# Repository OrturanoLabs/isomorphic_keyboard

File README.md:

# Isomorphic keyboard

An open-source, **modular isomorphic keyboard**. The instrument is built from identical
12-key tiles arranged in supported column-based grids. A pico-ice (Lattice iCE40UP5K)
rediscovers the arrangement on every scan and plays it over **MIDI**. Tiles can be added,
removed and moved while playing.

## Status

- **rev A** (tag `rev-a-prototype`): working prototype. Double-stack tiles (key board over
  logic board), hot-plug, automatic above/below/beside detection, MIDI DIN output.
- **Current development:** a single-PCB tile with Cherry-MX-style SMD hot-swap
  sockets, a practical equilateral lattice and chassis-supported drop-in contacts.
  The **tiny FPGA is the lead implementation**, with discrete logic retained as
  the no-programmer reference and alternative. Target: 20 MHz shift clock,
  up to 16 tiles; no tile-side MCU, LEDs or Hall sensing.
- **rev B** (reference commit `d358953`): termination, decoupling and assembly
  studies for the earlier double-board design; not hardware-tested.

The project is consolidated into this one directory. Start with the
[current status](docs/architecture/current-development.md) and
[ordered FPGA plan](docs/FPGA_PLAN.md); migration details are in the
[consolidation record](docs/CONSOLIDATION.md). The FPGA/controller tests have
advanced, but the new tile is not yet a routed, hardware-validated release.

## Repository layout

| Path | Content |
|---|---|
| `docs/` | documentation: [index](docs/index.md), [engineering ledger](docs/LEDGER.md) |
| `hardware/experiments/simple-tile/fpga/` | active FPGA RTL, chain tests and board prototype |
| `hardware/experiments/simple-tile/discrete-spld/` | discrete baseline; SPLD comparison retained as reference |
| `hardware/experiments/simple-tile/connector-next/` | current chassis-contact and tiling study |
| `hardware/kicad/tile/` | reference KiCad key board + logic board |
| `hardware/simulation/` | behavioural VHDL model of a tile and grid testbenches |
| `hardware/fabrication/rev-a/` | gerbers and BOM of the manufactured rev-A boards |
| `firmware/ice40/` | controller firmware (VHDL) for the pico-ice |
| `firmware/ice40/scan20/` | isolated 20 MHz / 16-tile scan-engine test fixture |
| `firmware/experiments/` | earlier bring-up designs, kept for reference |
| `tools/` | rootless container recipes, `kicad-cli` / OSS CAD Suite wrappers, check scripts |
| `LICENSES/` | full license texts |

## Quick start

Current development checks, from the repository root:

```sh
bash hardware/experiments/simple-tile/fpga/sim/run_sims.sh
bash firmware/ice40/scan20/sim/run_sims.sh
```

The following commands build/open the earlier reference implementation:

```sh
# firmware (rootless podman)
podman build -t localhost/oss-cad-suite:2026-09-26 tools/containers/oss-cad-suite
cd firmware/ice40 && ../../tools/oss.sh make && make upload-flash

# hardware
flatpak install --user flathub org.kicad.KiCad
flatpak run org.kicad.KiCad hardware/kicad/tile/isomorphic_tile.kicad_pro
```

See [docs/build/firmware.md](docs/build/firmware.md) and
[docs/build/hardware.md](docs/build/hardware.md).

## Licenses

| Part | License |
|---|---|
| Hardware (`hardware/`) | CERN-OHL-S v2 |
| Firmware and tools (`firmware/`, `tools/`) | GPL-3.0 |
| Documentation (`docs/`) | CC BY 4.0 |
| Vendored Open Logic subset (`firmware/ice40/src/open-logic/`) | PSI HDL Library License 1.0 |

Full texts are in `LICENSES/`. Each top-level folder has its own `LICENSE.md`.

© Orturano Labs

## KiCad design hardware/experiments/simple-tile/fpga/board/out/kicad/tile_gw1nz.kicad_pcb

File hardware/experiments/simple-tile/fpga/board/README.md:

# fpga/board -- single-PCB FPGA tile: placement + circuit prototype

Owner: fpga-board worker. Package/board facts come from vendor documents
(sha256-stamped in `data/*.json`) and machine checks in `tools/`; nothing
here is inferred from synthesis tool behavior.

## Layout

- `data/pins_gw1nz_qn48.json`, `data/pins_ice40up_sg48.json` -- per-pin
  provenance DBs (role, rail, vendor doc + section + sha256) for the two
  candidates. Pin 9 (GW1NZ) is excluded: automotive UG846 disagrees with
  commercial UG842 on it (VCC vs IOR2A) -- order-code hazard.
- `constraints/tile_gw1nz_board.cst`, `tile_up5k_board.pcf` -- PRODUCTION
  pin maps (26 tile IOs verified against the vendor tables; JTAG/config/
  strap pads reserved). These supersede `fpga/synth/*` (empirical chipdb
  probe proposals). Do not edit `fpga/**` from here.
- `kicad/board_gen.py` -- deterministic board builder (corrected revc
  TileTiling outline, 12 Kailh sockets, 19 connector-next chassis pads,
  passives, TPs), self-check gates GK1..GK7.
- `kicad/gen_footprints.py` -- the two custom QFN48 footprints.
- `kicad/lib/fpga_board.pretty/` -- generated custom footprints.
- `tools/pincon_check.py` -- constraint-vs-vendor-table checker (B1..B6,
  H1, S1; both variants PASS).
- `tools/footprint_verify.py` -- footprint land pattern vs vendor package
  dims, incl. negative control (both PASS; UP5K land = LAND-TBD).
- `tools/board_net_check.py` -- netlist/power-pin binding checker on the
  emitted .kicad_pcb, incl. negative controls (both PASS).
- `tools/run_board_pnr.sh` -- real yosys/nextpnr PnR of the fpga
  workstream's RTL (read-only) against the production maps (PASS;
  `RUN_VARIANTS="gw1nz"` narrows a re-run when only one cst changed).
- `kicad/sch_gen.py` -- authoritative schematic generator (gw1nz):
  emits `out/kicad/tile_gw1nz.kicad_sch` + local symbol lib. TRUE KiCad
  ERC at severity-all = **0 violations, no exclusions**
  (`out/kicad/tile_gw1nz.erc.json`).
- `tools/schematic_check.py` -- schematic<->board<->cst reconciliation
  S1..S7 + 3 negative controls (fresh ERC rerun, 45-net census,
  pad parity 144==144, cst port<->net<->pin mapping, strap + series
  node-set checks) -- PASS.
- `tools/drive_attr_ab.sh` -- durable proof that VHDL `attribute DRIVE`
  reaches the bitstream through the OSS flow while cst attrs are dead
  (fs_A==production hash, fs_B differs in exactly the 5 OBUF/TBUF cells).
- `tools/quote_prep.py` -- distributor-agnostic quote-package preparation:
  emits `docs/quote/bom_neutral.csv` + `docs/quote/cpl_gw1nz_provisional.csv`
  from the current pcb + bom.json with self-checks (census 65, ref parity,
  Value drift). Preparation for the BLOCKED quote gate; the board is
  still an unrouted prototype and the final CPL comes from KiCad's own
  exporter after routing.
- `tools/netclass_prep.py` -- FPGA-02 preparation: machine-checked
  net-class assignment of all 45 r6 nets (edge/level_out/channel_in/
  keys/power/config) with the strict reference rules, emitting
  `docs/netclasses.json` (self-checks N1-N5: exact partition, series
  topology re-read off the pcb, vacuity control). Preparation only.
- `docs/candidate.md`, `docs/power_reg.md`, `docs/readiness.md`,
  `docs/termination.md`, `docs/bom.md`/`docs/bom.json` -- decision,
  rails/straps/regulator (incl. r6 decoupling-placement table +
  load/thermal budget closure), honest gate ledger + open gaps, output
  termination decision-record (19 contacts kept; r6 series-R positions
  R7..R11 0R-populated; RTL DRIVE = proven free knob; cst attrs =
  UNVERIFIED vendor hints), and sourced BOM with the not-obtained-quote
  blocker recorded.
- `docs/quote/` -- quote-package checklist + generated neutral BOM /
  provisional CPL (2026-10-15; quote itself still NOT OBTAINED, needs
  account + upload on the routed board).
- `docs/routing_plan.md` -- FPGA-02 preparation: r6 routing census,
  measured escape geometry, rule-set candidates and the 2L-vs-4L
  comparison procedure (preparation only; FPGA-02 stays pending).
- `out/` -- regenerated artifacts (json/md/logs, placement txt, DRC, PnR).

## Regenerate / re-verify

```
python3 kicad/board_gen.py                 # ~10 min; emits out/kicad/*
python3 kicad/sch_gen.py                   # emits out/kicad/tile_gw1nz.kicad_sch + lib
python3 tools/footprint_verify.py          # land pattern vs vendor dims
python3 tools/pincon_check.py              # constraints vs vendor tables
python3 tools/board_net_check.py           # emitted-board netlist check
python3 tools/schematic_check.py           # sch<->board<->cst S1..S7 (reruns ERC)
tools/oss.sh bash hardware/experiments/simple-tile/fpga/board/tools/run_board_pnr.sh
tools/kicad-cli.sh pcb drc --format json -o out/kicad/tile_gw1nz.drc.json out/kicad/tile_gw1nz.kicad_pcb
tools/kicad-cli.sh pcb drc --format json -o out/kicad/tile_up5k.drc.json out/kicad/tile_up5k.kicad_pcb
```

## Status (2026-10-15, board r6)

Both boards are **placement-prototype clean** (0 DRC errors; unconnected
counts = unrouted nets by design; silkscreen-class warnings remain).
Electrical design is **scoped and verified at the gates above**: core
regulator selected + pinout-verified (TLV75512PDBVR), authoritative
schematic at TRUE ERC = 0 with schematic<->board<->cst parity proven
(incl. the r6 series-R split, 45 nets / 144 pads), output termination
decision-recorded with a frame-neutral mitigation implemented (R7..R11
0402 0R-populated positions -- placement proven, NOT routed proof).
Boards are still **not routed and not fab-ready**, the PCBA assembly
quote is **not obtained** (ordered FPGA-01/5 requirement, no waiver),
and FPGA-01 stays **IN PROGRESS** -- see `docs/readiness.md` and
`docs/bom.md`.

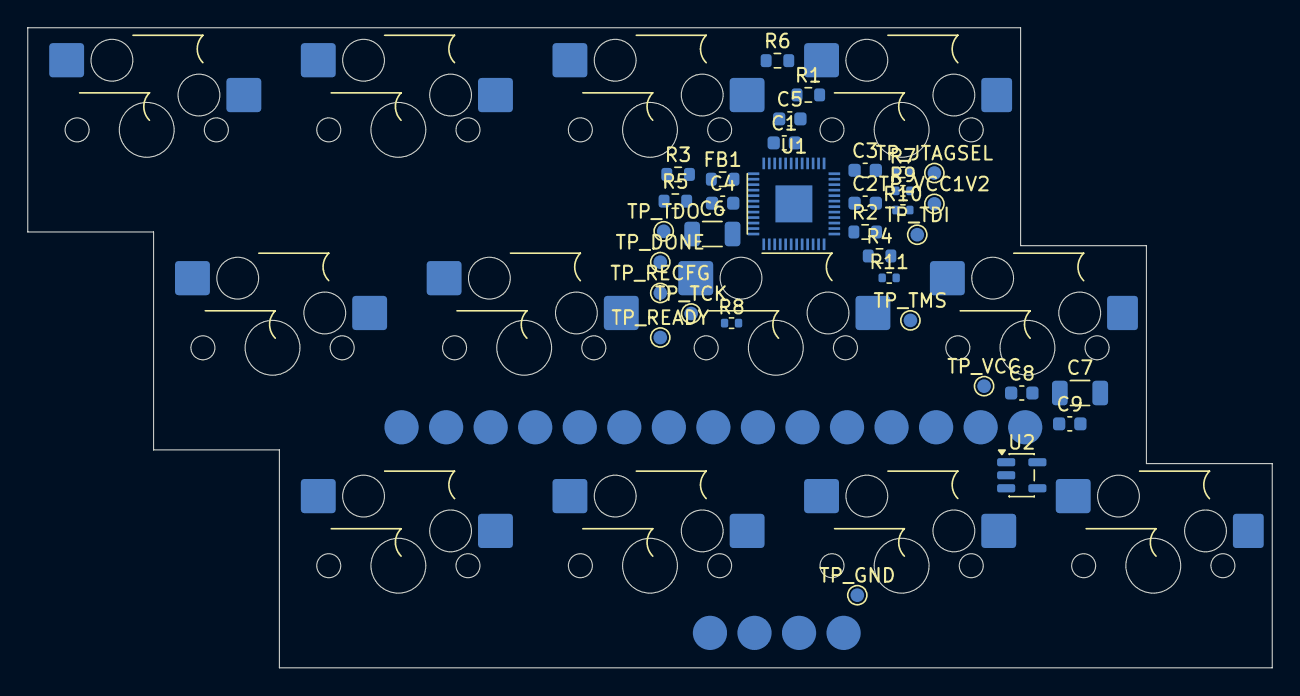
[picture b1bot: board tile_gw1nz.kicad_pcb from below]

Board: 2 copper layers, 90.8 x 46.7 mm, 65 parts (53 on the bottom side), 45 nets, no tracks yet.

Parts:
C1: 100n; C1
C2: 100n; C2
C3: 100n; C3
C4: 100n; C4
C5: 100n; C5
C6: 4u7; C6
C7: 4u7; C7
C8: 1u; C8
C9: 1u; C9
FB1: FB 120R@100M; FB1
JP_B_W: PAD2.5; JP_B_W
JP_B_clk: PAD2.5; JP_B_clk
JP_B_data: PAD2.5; JP_B_data
JP_B_first: PAD2.5; JP_B_first
JP_B_latch: PAD2.5; JP_B_latch
JP_GND: PAD2.5; JP_GND
JP_GND_DET_B: PAD2.5; JP_GND_DET_B
JP_GND_DET_R: PAD2.5; JP_GND_DET_R
JP_GND_DET_T: PAD2.5; JP_GND_DET_T
JP_L_clk: PAD2.5; JP_L_clk
JP_L_data: PAD2.5; JP_L_data
JP_L_endrow: PAD2.5; JP_L_endrow
JP_L_latch: PAD2.5; JP_L_latch
JP_R_latch: PAD2.5; JP_R_latch
JP_T_W: PAD2.5; JP_T_W
JP_T_clk: PAD2.5; JP_T_clk
JP_T_data: PAD2.5; JP_T_data
JP_T_endcol: PAD2.5; JP_T_endcol
JP_VCC: PAD2.5; JP_VCC
R1: 1k; R1
R2: 1k; R2
R3: 4k7; R3
R4: 4k7; R4
R5: 4k7; R5
R6: 4k7; R6
R7: 0R; R7
R8: 0R; R8
R9: 0R; R9
R10: 0R; R10
R11: 0R; R11
SW1: Kailh MX hotswap; SW1
SW2: Kailh MX hotswap; SW2
SW3: Kailh MX hotswap; SW3
SW4: Kailh MX hotswap; SW4
SW5: Kailh MX hotswap; SW5
SW6: Kailh MX hotswap; SW6
SW7: Kailh MX hotswap; SW7
SW8: Kailh MX hotswap; SW8
SW9: Kailh MX hotswap; SW9
SW10: Kailh MX hotswap; SW10
SW11: Kailh MX hotswap; SW11
SW12: Kailh MX hotswap; SW12
TP_DONE: CFG_DONE; TP_DONE
TP_GND: GND; TP_GND
TP_JTAGSEL: JTAGSEL_N; TP_JTAGSEL
TP_READY: CFG_READY; TP_READY
TP_RECFG: CFG_RECONFIG; TP_RECFG
TP_TCK: JTAG_TCK; TP_TCK
TP_TDI: JTAG_TDI; TP_TDI
TP_TDO: JTAG_TDO; TP_TDO
TP_TMS: JTAG_TMS; TP_TMS
TP_VCC: VCC; TP_VCC
TP_VCC1V2: VCC1V2; TP_VCC1V2
U1: GW1NZ-LV1QN48C6/I5; U1
U2: TLV75512PDBVR; U2

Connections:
B_W: JP_B_W.1, R11.2
B_W_DRV: R11.1, U1.27
B_clk: JP_B_clk.1, U1.47
B_data: JP_B_data.1, R10.2
B_data_DRV: R10.1, U1.30
B_first: JP_B_first.1, U1.40
B_latch: JP_B_latch.1, U1.22
CFG_DONE: R5.1, TP_DONE.1, U1.46
CFG_READY: R4.1, TP_READY.1, U1.45
CFG_RECONFIG: R6.1, TP_RECFG.1, U1.48
GND: C1.2, C2.2, C3.2, C4.2, C5.2, C6.2, C7.2, C8.2, C9.2, JP_GND.1, JP_GND_DET_B.1, JP_GND_DET_R.1, JP_GND_DET_T.1, R1.2, R2.2, R3.2, TP_GND.1, U1.2, U1.26, U1.49, U2.2
JTAGSEL_N: TP_JTAGSEL.1, U1.44
JTAG_TCK: R3.1, TP_TCK.1, U1.3
JTAG_TDI: TP_TDI.1, U1.5
JTAG_TDO: TP_TDO.1, U1.7
JTAG_TMS: TP_TMS.1, U1.4
K1: SW1.2, U1.8
K2: SW2.2, U1.10
K3: SW3.2, U1.11
K4: SW4.2, U1.13
K5: SW5.2, U1.16
K6: SW6.2, U1.17
K7: SW7.2, U1.18
K8: SW8.2, U1.20
K9: SW9.2, U1.21
K10: SW10.2, U1.23
K11: SW11.2, U1.33
K12: SW12.2, U1.34
L_clk: JP_L_clk.1, R8.2
L_clk_DRV: R8.1, U1.19
L_data: JP_L_data.1, U1.24
L_endrow: JP_L_endrow.1, U1.41
L_latch: JP_L_latch.1, R9.2
L_latch_DRV: R9.1, U1.31
MODE0: R1.1, U1.43
MODE1: R2.1, U1.42
R_latch: JP_R_latch.1, U1.32
T_W: JP_T_W.1, U1.38
T_clk: JP_T_clk.1, R7.2
T_clk_DRV: R7.1, U1.35
T_data: JP_T_data.1, U1.28
T_endcol: JP_T_endcol.1, U1.39
VCC: C1.1, C2.1, C3.1, C7.1, C9.1, JP_VCC.1, R4.2, R5.2, R6.2, SW1.1, SW2.1, SW3.1, SW4.1, SW5.1, SW6.1, SW7.1, SW8.1, SW9.1, SW10.1, SW11.1, SW12.1, TP_VCC.1, U1.1, U1.25, U1.36, U2.1, U2.3
VCC1V2: C4.1, C5.1, C6.1, FB1.2, TP_VCC1V2.1, U1.12, U1.37
VCC1V2_RAW: C8.1, FB1.1, U2.5

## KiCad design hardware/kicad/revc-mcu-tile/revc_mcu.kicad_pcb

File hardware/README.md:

# Hardware

| Folder | Content |
|---|---|
| `kicad/tile/` | KiCad project `isomorphic_tile`: key board (12 Cherry MX keys) and logic board (shift registers, chaining logic, edge connectors), fabricated as one panel |
| `simulation/` | behavioural VHDL model of a tile (`tile.vhdl`, `74hc165.vhdl`) and grid testbenches (`tile_tb*.vhdl`); run with `make` (GHDL), view with GTKWave |
| `fabrication/rev-a/` | gerbers and BOM of the rev-A boards as manufactured |

Start with [docs/architecture/overview.md](../docs/architecture/overview.md) and
[docs/build/hardware.md](../docs/build/hardware.md). The latter covers the mandatory
ERC/DRC/invariant checks.

License: CERN-OHL-S v2 (see `LICENSE.md`).

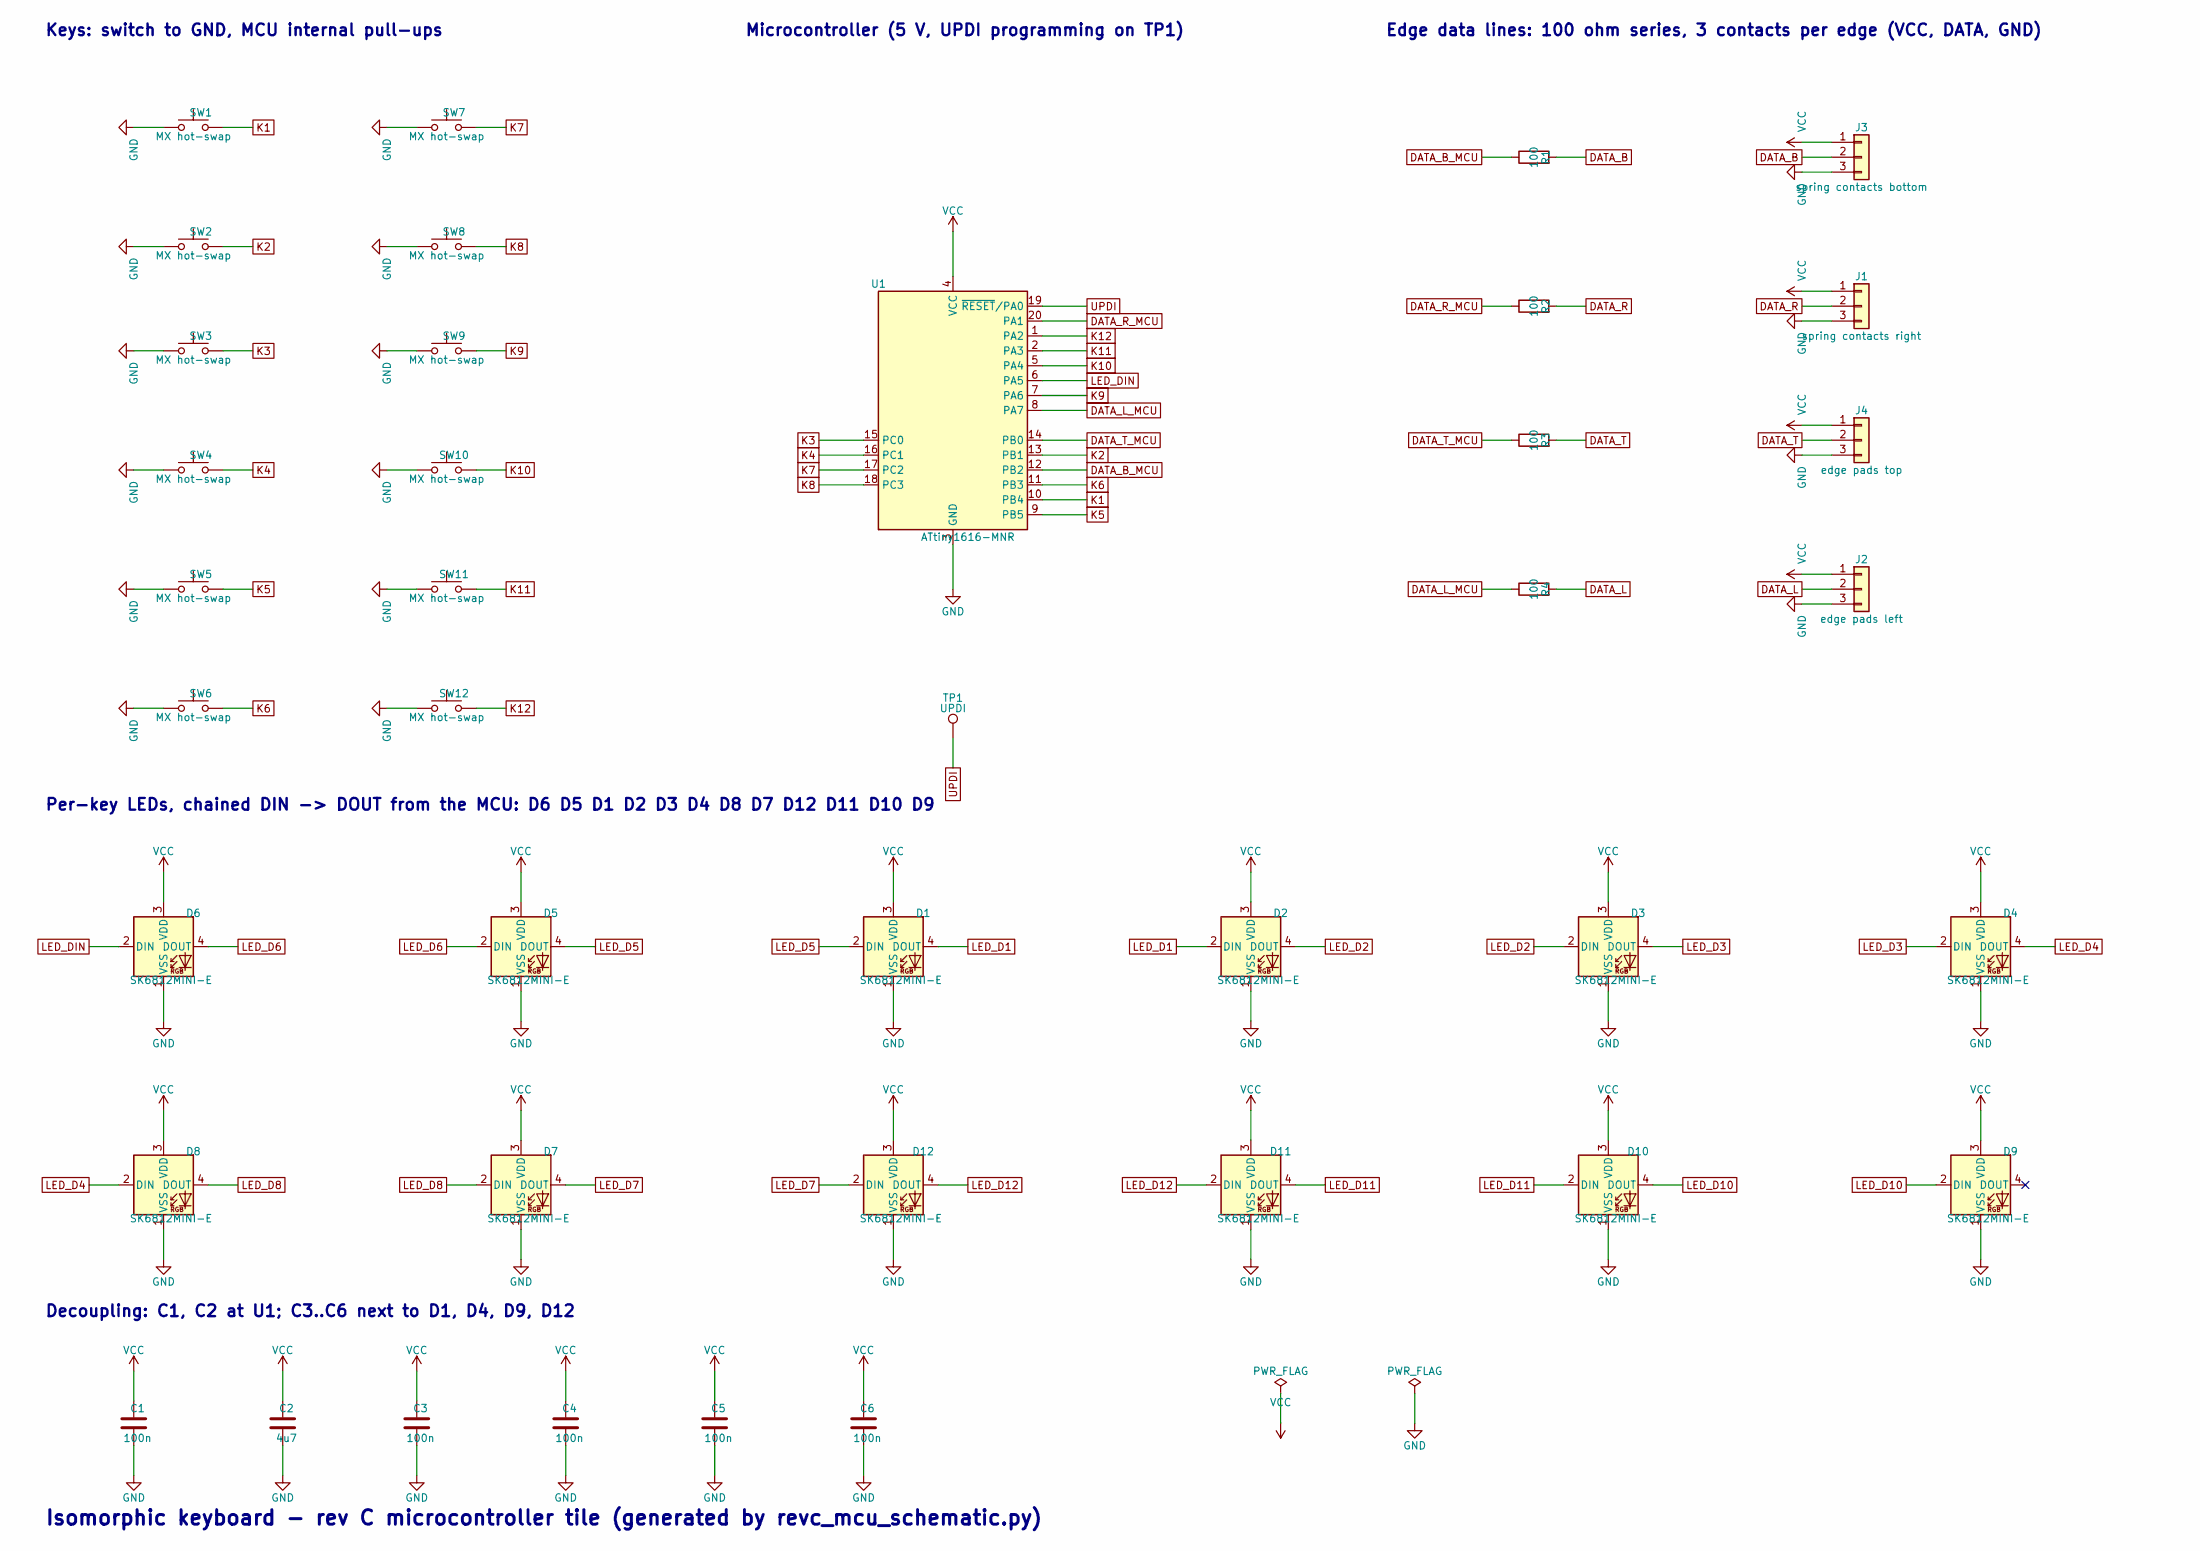
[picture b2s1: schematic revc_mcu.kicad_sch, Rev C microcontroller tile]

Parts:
C1, C3, C4, C5, C6: 100n; C_0603_1608Metric; MPN CL10B104KB8NNNC
C2: 4u7; C_0805_2012Metric; MPN CL21A475KAQNNNE
D1, D2, D3, D4, D5, D6, D7, D8, D9, D10, D11, D12: SK6812MINI-E; LED_SK6812MINI-E_3.2x2.8mm_P1.5mm_ReverseMount; MPN SK6812MINI-E
J1: spring contacts right; EdgeContacts_right
J2: edge pads left; EdgeContacts_left
J3: spring contacts bottom; EdgeContacts_bottom
J4: edge pads top; EdgeContacts_top
R1, R2, R3, R4: 100; R_0603_1608Metric; MPN RC0603FR-07100RL
SW1, SW2, SW3, SW4, SW5, SW6, SW7, SW8, SW9, SW10, SW11, SW12: MX hot-swap; SW_Hotswap_Kailh_MX_1.00u_EdgeTrim; MPN CPG151101S11
TP1: UPDI; TestPoint_Pad_D1.5mm
U1: ATtiny1616-MNR; VQFN-20-1EP_3x3mm_P0.4mm_EP1.7x1.7mm; MPN ATTINY1616-MNR

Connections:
DATA_B: J3.2, R1.2
DATA_B_MCU: R1.1, U1.12 (PB2)
DATA_L: J2.2, R4.2
DATA_L_MCU: R4.1, U1.8 (PA7)
DATA_R: J1.2, R2.2
DATA_R_MCU: R2.1, U1.20 (PA1)
DATA_T: J4.2, R3.2
DATA_T_MCU: R3.1, U1.14 (PB0)
GND: C1.2, C2.2, C3.2, C4.2, C5.2, C6.2, D1.1 (VSS), D2.1 (VSS), D3.1 (VSS), D4.1 (VSS), D5.1 (VSS), D6.1 (VSS), D7.1 (VSS), D8.1 (VSS), D9.1 (VSS), D10.1 (VSS), D11.1 (VSS), D12.1 (VSS), J1.3, J2.3, J3.3, J4.3, SW1.1, SW2.1, SW3.1, SW4.1, SW5.1, SW6.1, SW7.1, SW8.1, SW9.1, SW10.1, SW11.1, SW12.1, U1.3 (GND), U1.21 (GND)
K1: SW1.2, U1.10 (PB4)
K2: SW2.2, U1.13 (PB1)
K3: SW3.2, U1.15 (PC0)
K4: SW4.2, U1.16 (PC1)
K5: SW5.2, U1.9 (PB5)
K6: SW6.2, U1.11 (PB3)
K7: SW7.2, U1.17 (PC2)
K8: SW8.2, U1.18 (PC3)
K9: SW9.2, U1.7 (PA6)
K10: SW10.2, U1.5 (PA4)
K11: SW11.2, U1.2 (PA3)
K12: SW12.2, U1.1 (PA2)
LED_D1: D1.4 (DOUT), D2.2 (DIN)
LED_D2: D2.4 (DOUT), D3.2 (DIN)
LED_D3: D3.4 (DOUT), D4.2 (DIN)
LED_D4: D4.4 (DOUT), D8.2 (DIN)
LED_D5: D1.2 (DIN), D5.4 (DOUT)
LED_D6: D5.2 (DIN), D6.4 (DOUT)
LED_D7: D7.4 (DOUT), D12.2 (DIN)
LED_D8: D7.2 (DIN), D8.4 (DOUT)
LED_D10: D9.2 (DIN), D10.4 (DOUT)
LED_D11: D10.2 (DIN), D11.4 (DOUT)
LED_D12: D11.2 (DIN), D12.4 (DOUT)
LED_DIN: D6.2 (DIN), U1.6 (PA5)
UPDI: TP1.1, U1.19 (~RESET/PA0)
VCC: C1.1, C2.1, C3.1, C4.1, C5.1, C6.1, D1.3 (VDD), D2.3 (VDD), D3.3 (VDD), D4.3 (VDD), D5.3 (VDD), D6.3 (VDD), D7.3 (VDD), D8.3 (VDD), D9.3 (VDD), D10.3 (VDD), D11.3 (VDD), D12.3 (VDD), J1.1, J2.1, J3.1, J4.1, U1.4 (VCC)

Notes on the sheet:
Keys: switch to GND, MCU internal pull-ups
Microcontroller (5 V, UPDI programming on TP1)
Edge data lines: 100 ohm series, 3 contacts per edge (VCC, DATA, GND)
Per-key LEDs, chained DIN -> DOUT from the MCU: D6 D5 D1 D2 D3 D4 D8 D7 D12 D11 D10 D9
Decoupling: C1, C2 at U1; C3..C6 next to D1, D4, D9, D12
Isomorphic keyboard - rev C microcontroller tile (generated by revc_mcu_schematic.py)

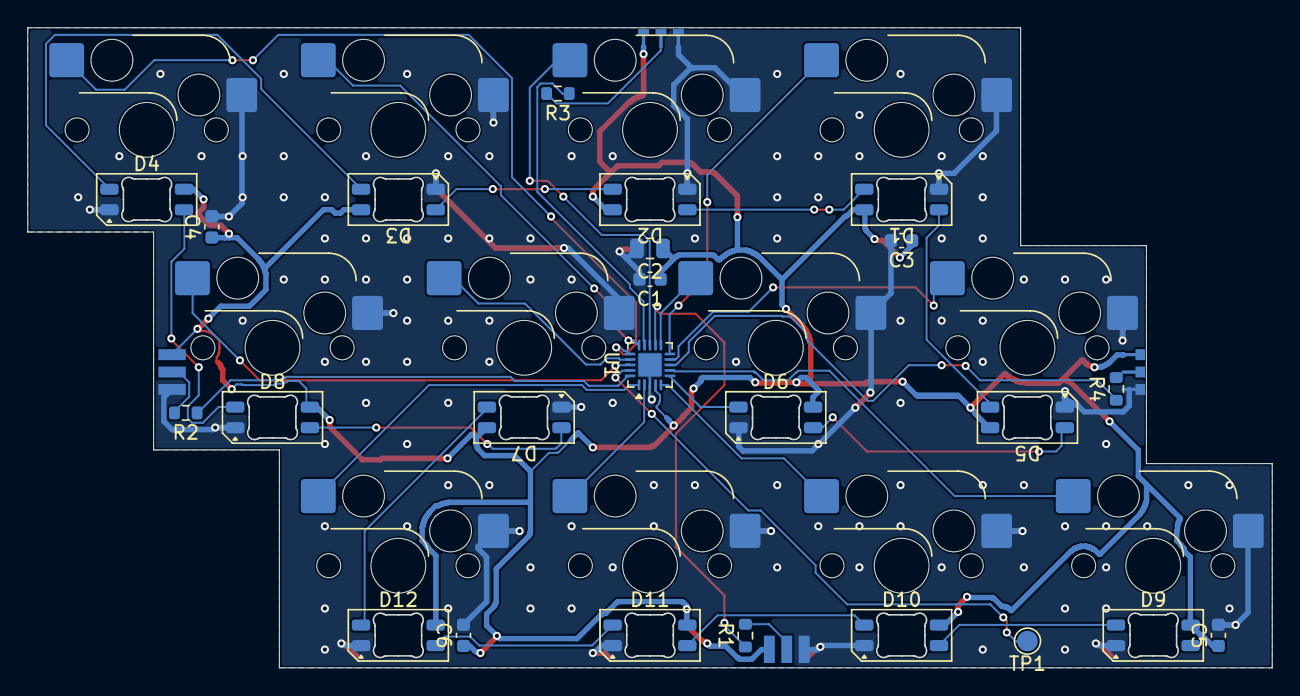
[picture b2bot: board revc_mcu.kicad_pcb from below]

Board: 2 copper layers, 90.8 x 46.7 mm, 40 parts (28 on the bottom side), 35 nets.

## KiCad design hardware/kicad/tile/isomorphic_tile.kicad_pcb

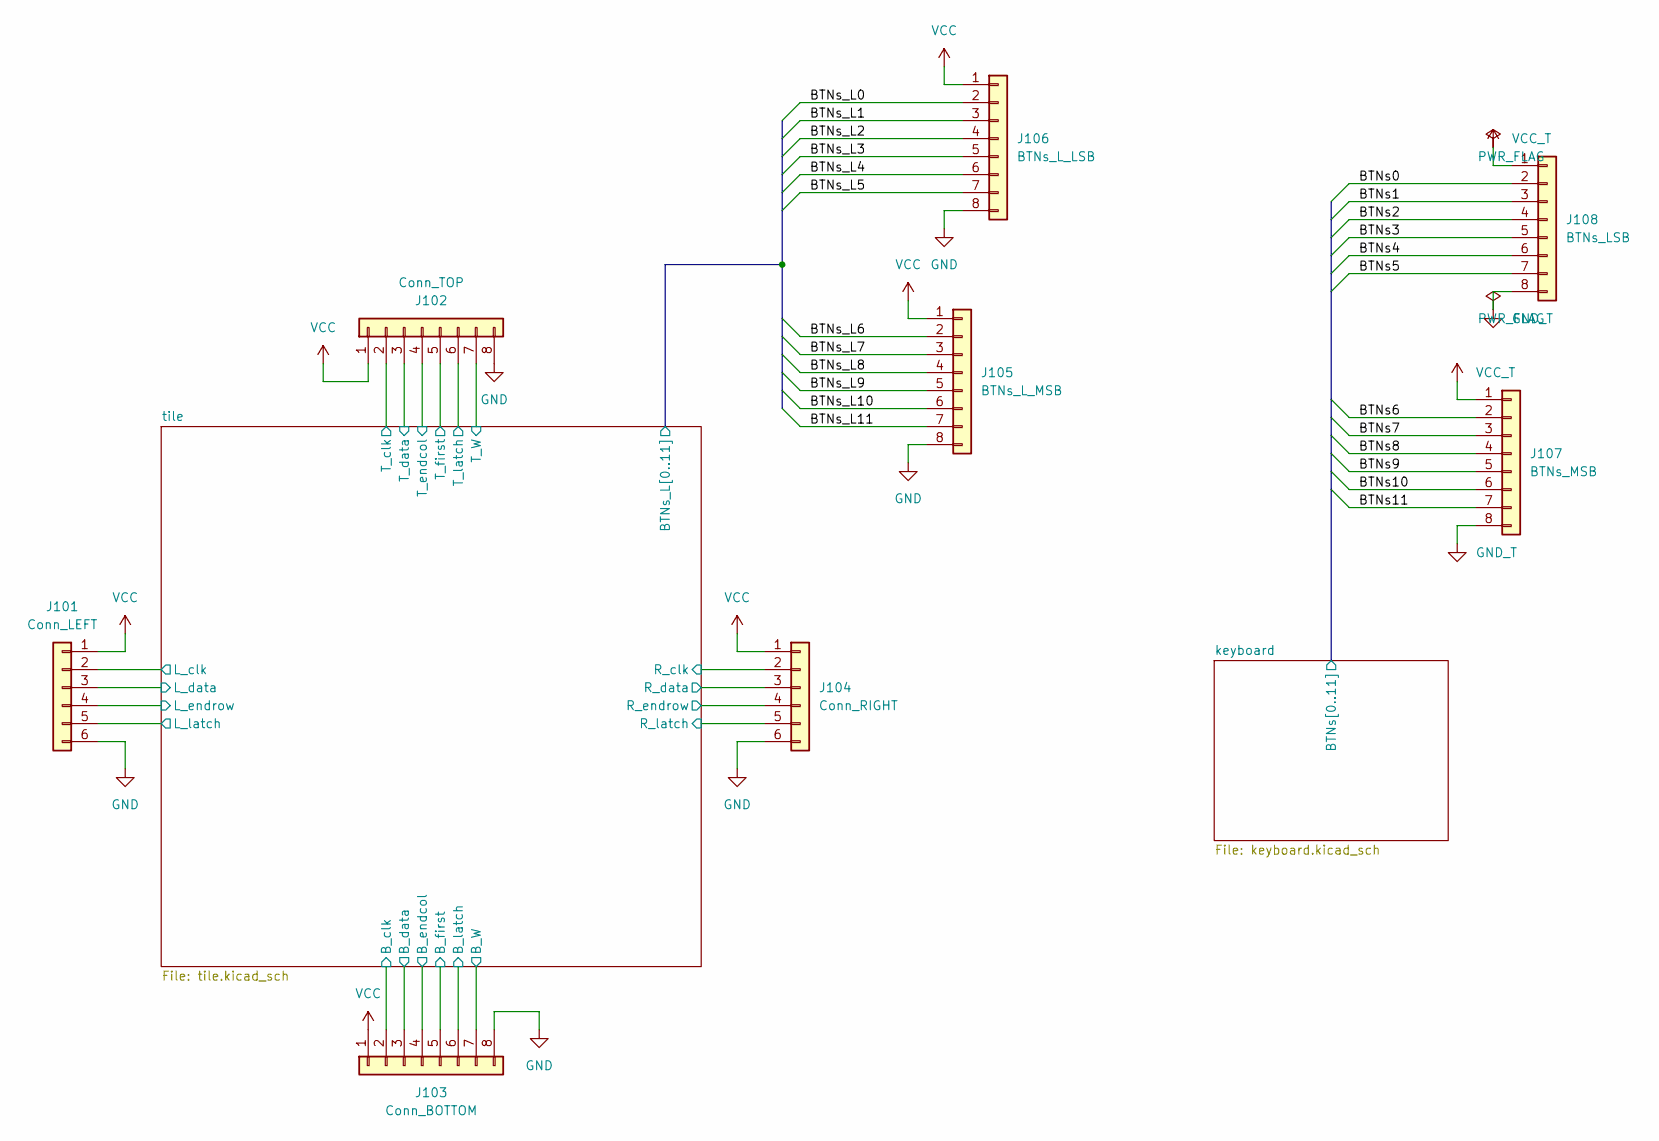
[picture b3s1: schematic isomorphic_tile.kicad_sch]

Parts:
J101: Conn_LEFT; PinSocket_1x06_P2.54mm_Horizontal; MPN 613010143121
J102: Conn_TOP; PinSocket_1x08_P2.54mm_Horizontal; MPN 613010143121
J103: Conn_BOTTOM; PinHeader_1x08_P2.54mm_Horizontal; MPN 61300811021
J104: Conn_RIGHT; PinHeader_1x06_P2.54mm_Horizontal; MPN 61300811021
J105: BTNs_L_MSB; PinSocket_1x08_P2.54mm_Vertical
J106: BTNs_L_LSB; PinSocket_1x08_P2.54mm_Vertical
J107: BTNs_MSB; PinHeader_1x08_P2.54mm_Vertical
J108: BTNs_LSB; PinHeader_1x08_P2.54mm_Vertical

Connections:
/keyboard/BTNs0: J108.2; also elsewhere on the board
/keyboard/BTNs1: J108.3; also elsewhere on the board
/keyboard/BTNs2: J108.4; also elsewhere on the board
/keyboard/BTNs3: J108.5; also elsewhere on the board
/keyboard/BTNs4: J108.6; also elsewhere on the board
/keyboard/BTNs5: J108.7; also elsewhere on the board
/keyboard/BTNs6: J107.2; also elsewhere on the board
/keyboard/BTNs7: J107.3; also elsewhere on the board
/keyboard/BTNs8: J107.4; also elsewhere on the board
/keyboard/BTNs9: J107.5; also elsewhere on the board
/keyboard/BTNs10: J107.6; also elsewhere on the board
/keyboard/BTNs11: J107.7; also elsewhere on the board
/tile/BTNs_L0: J106.2; also elsewhere on the board
/tile/BTNs_L1: J106.3; also elsewhere on the board
/tile/BTNs_L2: J106.4; also elsewhere on the board
/tile/BTNs_L3: J106.5; also elsewhere on the board
/tile/BTNs_L4: J106.6; also elsewhere on the board
/tile/BTNs_L5: J106.7; also elsewhere on the board
/tile/BTNs_L6: J105.2; also elsewhere on the board
/tile/BTNs_L7: J105.3; also elsewhere on the board
/tile/BTNs_L8: J105.4; also elsewhere on the board
/tile/BTNs_L9: J105.5; also elsewhere on the board
/tile/BTNs_L10: J105.6; also elsewhere on the board
/tile/BTNs_L11: J105.7; also elsewhere on the board
/tile/B_W: J103.7; also elsewhere on the board
/tile/B_clk: J103.2, J104.2; also elsewhere on the board
/tile/B_data: J103.3; also elsewhere on the board
/tile/B_first: J103.5; also elsewhere on the board
/tile/B_latch: J103.6; also elsewhere on the board
/tile/L_clk: J101.2; also elsewhere on the board
/tile/L_data: J101.3; also elsewhere on the board
/tile/L_endrow: J101.4; also elsewhere on the board
/tile/L_latch: J101.5; also elsewhere on the board
/tile/R_data: J104.3; also elsewhere on the board
/tile/R_latch: J104.5; also elsewhere on the board
/tile/T_W: J102.7; also elsewhere on the board
/tile/T_clk: J102.2; also elsewhere on the board
/tile/T_data: J102.3; also elsewhere on the board
/tile/T_endcol: J102.4; also elsewhere on the board
/tile/T_latch: J102.6; also elsewhere on the board
GND: J101.6, J102.5, J102.8, J103.4, J103.8, J104.4, J104.6, J105.8, J106.8; also elsewhere on the board
GND_T: J107.8, J108.8; also elsewhere on the board
VCC: J101.1, J102.1, J103.1, J104.1, J105.1, J106.1; also elsewhere on the board
VCC_T: J107.1, J108.1; also elsewhere on the board

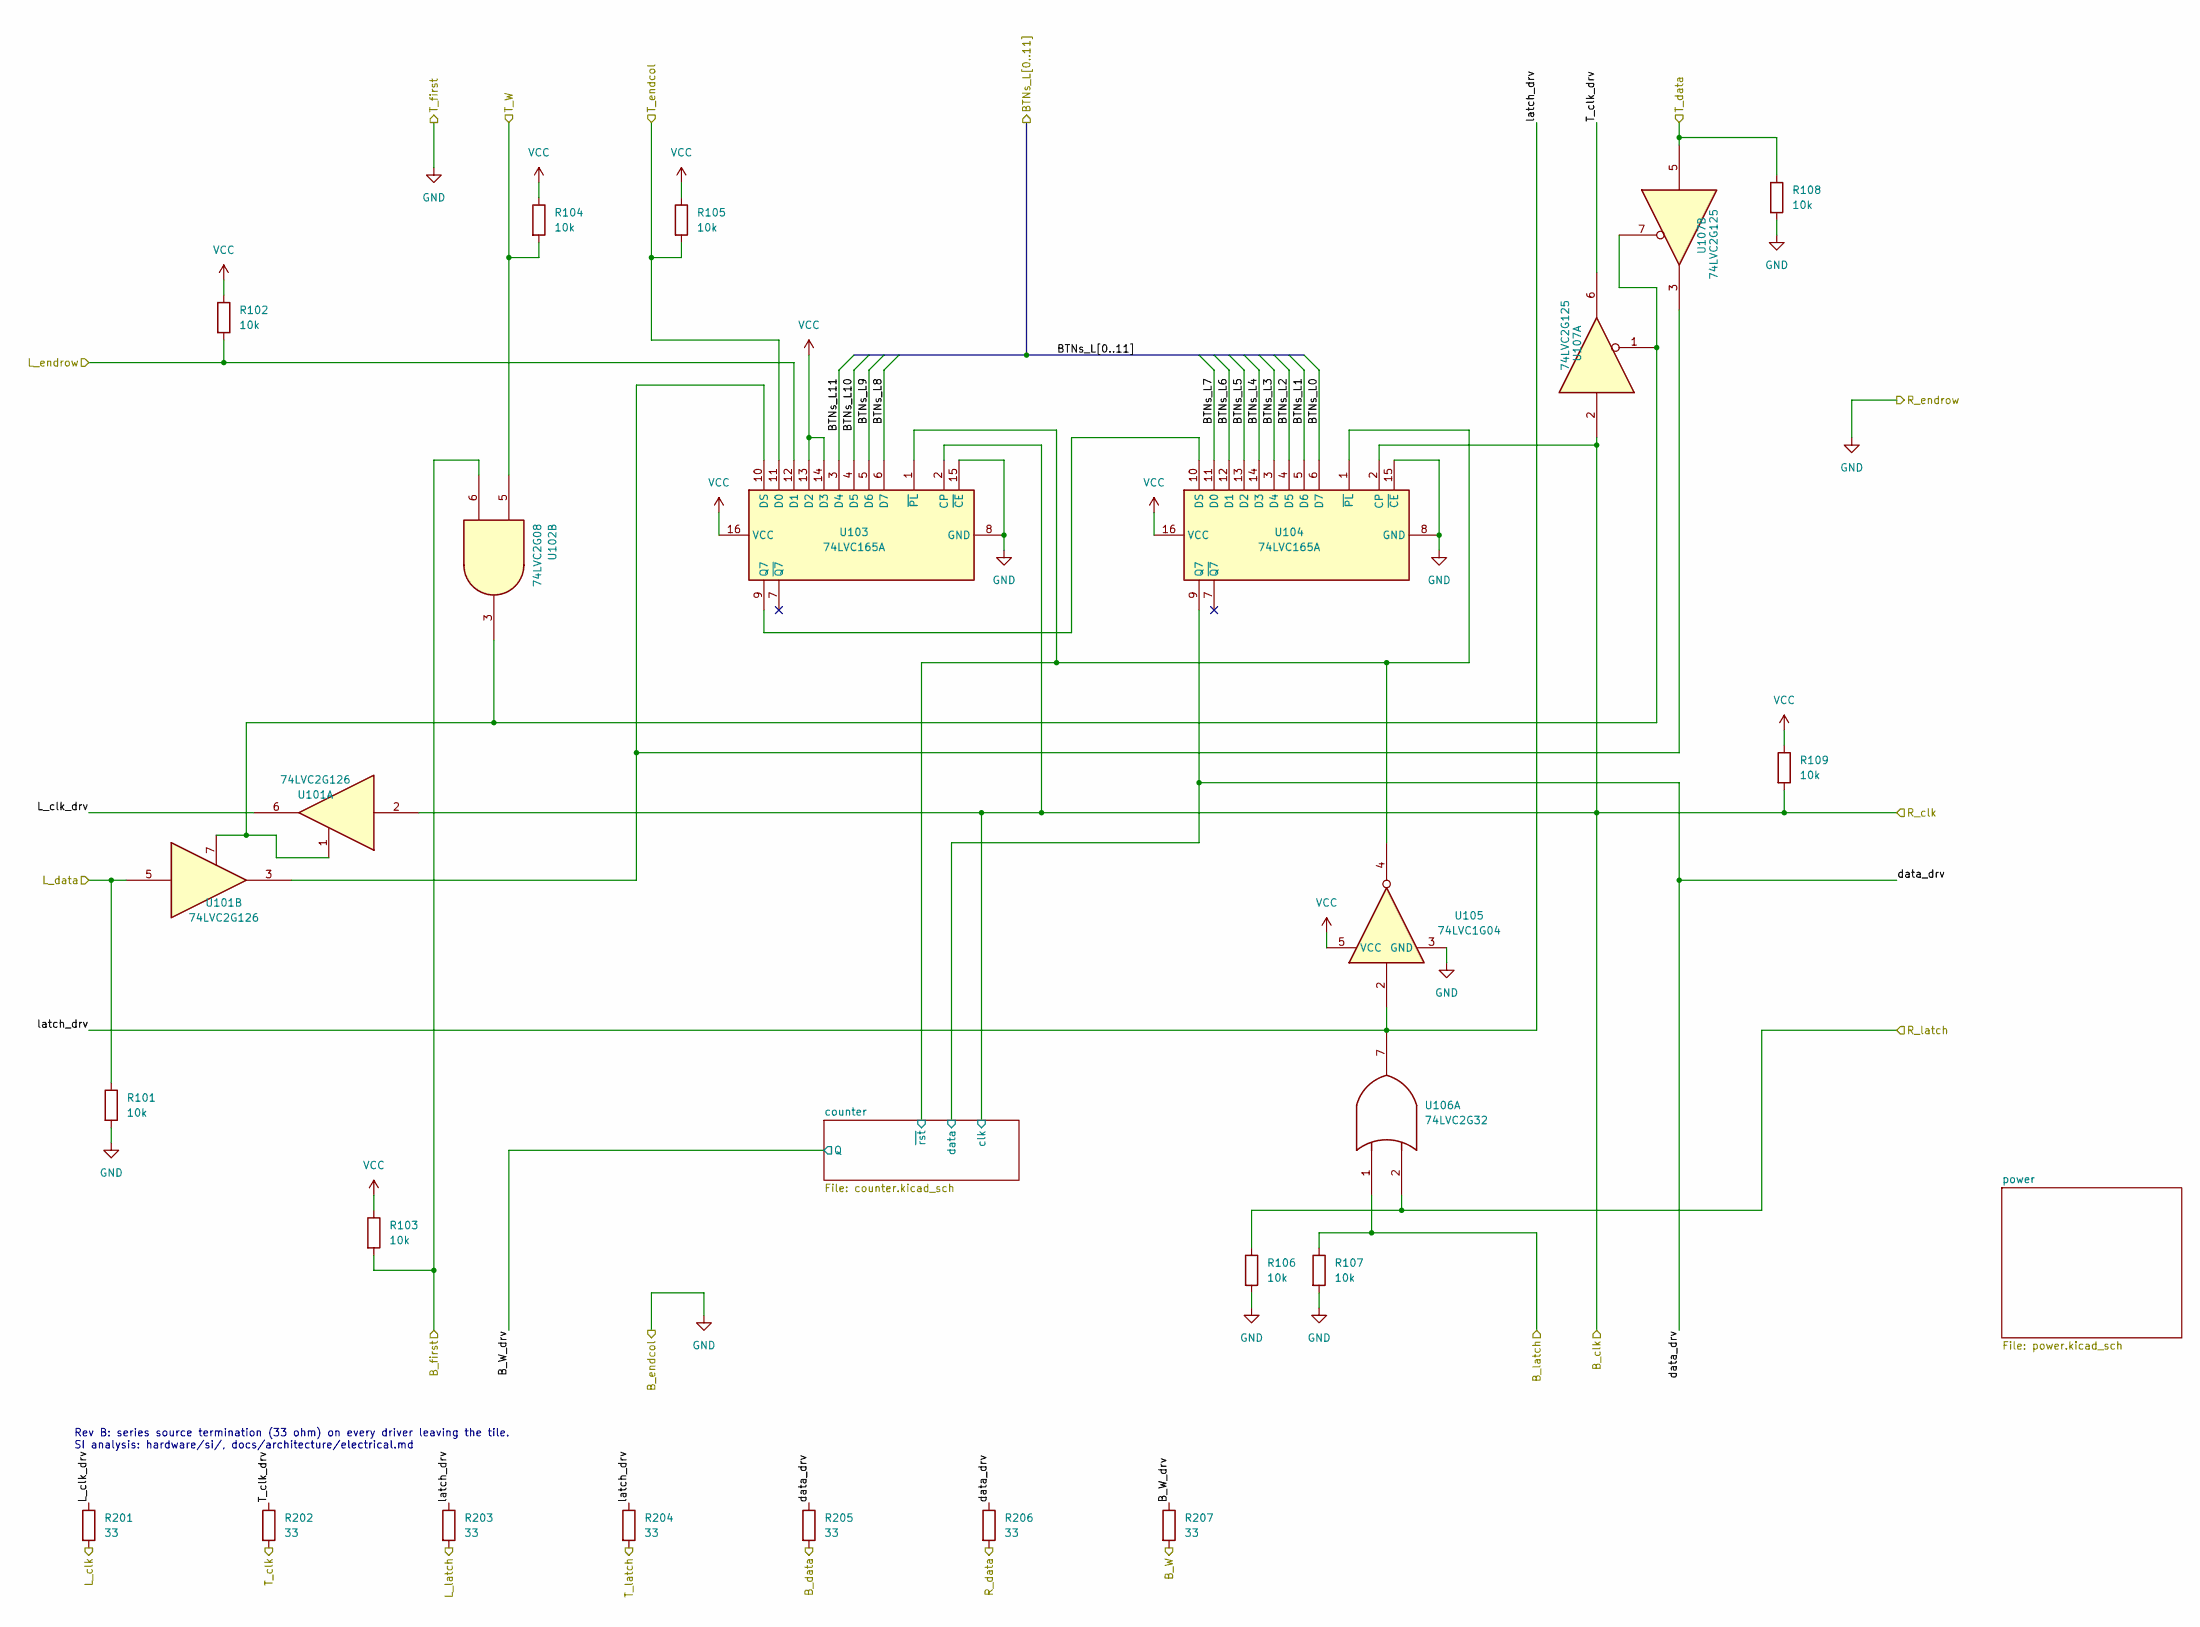
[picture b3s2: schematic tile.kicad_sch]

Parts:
R101, R102, R103, R104, R105, R106, R107, R108, R109: 10k; R_0603_1608Metric; MPN RC0603FR-0710KL
R201, R202, R203, R204, R205, R206, R207: 33; R_0603_1608Metric; MPN RC0603FR-0733RL
U101: 74LVC2G126; SSOP-8_2.95x2.8mm_P0.65mm; MPN SN74LVC2G126DCTR
U102: 74LVC2G08; SSOP-8_2.95x2.8mm_P0.65mm; MPN SN74LVC2G08DCTR
U103, U104: 74LVC165A; SOIC-16_3.9x9.9mm_P1.27mm; MPN SN74LVC165ADR
U105: 74LVC1G04; SOT-23-5; MPN SN74LVC1G04DBVR
U106: 74LVC2G32; SSOP-8_2.95x2.8mm_P0.65mm; MPN SN74LVC2G32DCTR
U107: 74LVC2G125; SSOP-8_2.95x2.8mm_P0.65mm; MPN SN74LVC2G125DCTR

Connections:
/tile/BTNs_L0: U104.6 (D7); also elsewhere on the board
/tile/BTNs_L1: U104.5 (D6); also elsewhere on the board
/tile/BTNs_L2: U104.4 (D5); also elsewhere on the board
/tile/BTNs_L3: U104.3 (D4); also elsewhere on the board
/tile/BTNs_L4: U104.14 (D3); also elsewhere on the board
/tile/BTNs_L5: U104.13 (D2); also elsewhere on the board
/tile/BTNs_L6: U104.12 (D1); also elsewhere on the board
/tile/BTNs_L7: U104.11 (D0); also elsewhere on the board
/tile/BTNs_L8: U103.6 (D7); also elsewhere on the board
/tile/BTNs_L9: U103.5 (D6); also elsewhere on the board
/tile/BTNs_L10: U103.4 (D5); also elsewhere on the board
/tile/BTNs_L11: U103.3 (D4); also elsewhere on the board
/tile/B_W: R207.2; also elsewhere on the board
/tile/B_W_drv: R207.1; also elsewhere on the board
/tile/B_clk: R109.2, U101.2, U103.2 (CP), U104.2 (CP), U107.2; also elsewhere on the board
/tile/B_data: R205.2; also elsewhere on the board
/tile/B_first: R103.2, U102.6; also elsewhere on the board
/tile/B_latch: R107.1, U106.1; also elsewhere on the board
/tile/L_clk: R201.2; also elsewhere on the board
/tile/L_clk_drv: R201.1, U101.6
/tile/L_data: R101.1, U101.5; also elsewhere on the board
/tile/L_endrow: R102.2, U103.12 (D1); also elsewhere on the board
/tile/L_latch: R203.2; also elsewhere on the board
/tile/R_data: R206.2; also elsewhere on the board
/tile/R_latch: R106.1, U106.2; also elsewhere on the board
/tile/T_W: R104.2, U102.5; also elsewhere on the board
/tile/T_clk: R202.2; also elsewhere on the board
/tile/T_clk_drv: R202.1, U107.6
/tile/T_data: R108.1, U107.5; also elsewhere on the board
/tile/T_endcol: R105.2, U103.11 (D0); also elsewhere on the board
/tile/T_latch: R204.2; also elsewhere on the board
/tile/counter/~rst: U103.1 (~PL), U104.1 (~PL), U105.4; also elsewhere on the board
/tile/data_drv: R205.1, R206.1, U104.9 (Q7); also elsewhere on the board
/tile/latch_drv: R203.1, R204.1, U105.2, U106.7
GND: R101.2, R106.2, R107.2, R108.2, U103.8 (GND), U103.15 (~CE), U104.8 (GND), U104.15 (~CE), U105.3 (GND); also elsewhere on the board
unnamed: U101.1, U101.7, U102.3, U107.1, U107.7
unnamed: U101.3, U103.10 (DS), U107.3
unnamed: U103.9 (Q7), U104.10 (DS)
VCC: R102.1, R103.1, R104.1, R105.1, R109.1, U103.13 (D2), U103.14 (D3), U103.16 (VCC), U104.16 (VCC), U105.5 (VCC); also elsewhere on the board

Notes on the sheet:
Rev B: series source termination (33 ohm) on every driver leaving the tile. SI analysis: hardware/si/, docs/architecture/electrical.md

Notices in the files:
hardware/experiments/simple-tile/fpga/board/kicad/board_gen.py:
SPDX-License-Identifier: GPL-3.0-only
